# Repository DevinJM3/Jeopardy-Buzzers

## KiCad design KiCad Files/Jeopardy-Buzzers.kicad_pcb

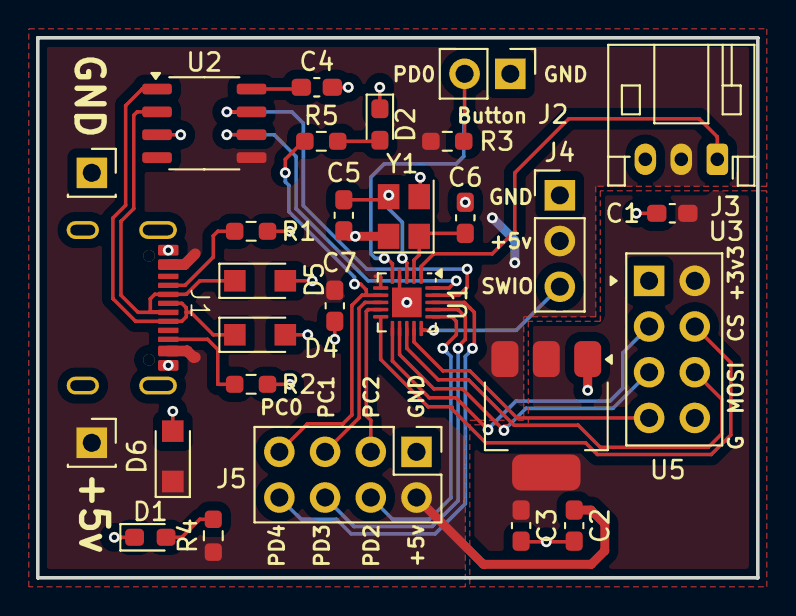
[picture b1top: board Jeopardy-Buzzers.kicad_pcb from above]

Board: 2 copper layers, 40.0 x 30.0 mm, 29 parts (0 on the bottom side), 28 nets.

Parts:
C1, C2: 10uF; C_0603_1608Metric_Pad1.08x0.95mm_HandSolder
C3: 22uF; C_0603_1608Metric_Pad1.08x0.95mm_HandSolder
C4, C7: 0.1uF; C_0603_1608Metric_Pad1.08x0.95mm_HandSolder
C5, C6: 12pF; C_0603_1608Metric_Pad1.08x0.95mm_HandSolder
D1, D2: LED; LED_0603_1608Metric_Pad1.05x0.95mm_HandSolder
D4, D5, D6: 5.1v; Nexperia_CFP3_SOD-123W
H1, H2: MountingHole_Pad; PinSocket_1x01_P2.54mm_Vertical
J1: USB_C_Receptacle_USB2.0_14P; Usb-C
J2: Conn_01x02_Pin; PinHeader_1x02_P2.54mm_Vertical
J3: Conn_01x03_Socket; JST_PH_S3B-PH-K_1x03_P2.00mm_Horizontal
J4: Conn_01x03_Socket; PinHeader_1x03_P2.54mm_Vertical
J5: Conn_02x04_Odd_Even; PinHeader_2x04_P2.54mm_Vertical
R1, R2: 5.1k; R_0603_1608Metric_Pad0.98x0.95mm_HandSolder
R3: 10k; R_0603_1608Metric_Pad0.98x0.95mm_HandSolder
R4, R5: 1k; R_0603_1608Metric_Pad0.98x0.95mm_HandSolder
U1: CH32V003FxUx; QFN-20-1EP_3x3mm_P0.4mm_EP1.65x1.65mm
U2: CH340N; SOP-8_3.9x4.9mm_P1.27mm
U3: NRF24L01_Breakout; nRF24L01_Breakout
U5: AMS1117-3.3; SOT-223-3_TabPin2
Y1: Crystal_24MHz; Crystal_SMD_3225-4Pin_3.2x2.5mm

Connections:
+3V3: C1.1, C3.1, U3.2 (VCC), U5.2 (VO)
+5V: C2.1, C7.2, D6.1 (K), H2.1, J1.A4 (VBUS), J3.2, J4.2, J5.2, R3.1, R4.1, U1.6 (VDD), U2.5 (VCC), U5.3 (VI)
GND: C1.2, C2.2, C3.2, C4.2, C5.2, C6.2, C7.1, D1.1 (K), D2.1 (K), D4.2 (A), D5.2 (A), D6.2 (A), H1.1, J1.A1 (GND), J2.1, J3.3, J4.1, J5.1, R1.2, R2.2, U1.4 (VSS), U1.21 (VSS), U2.3 (GND), U3.1 (GND), U3.8 (IRQ), U5.1 (GND), Y1.2, Y1.4
MCU_PC0: J5.7, R5.1, U1.7 (PC0)
MCU_PC1: J5.5, U1.8 (PC1)
MCU_PC2: J5.3, U1.9 (PC2)
MCU_PD2: J5.4, U1.16 (PD2)
MCU_PD3: J5.6, U1.17 (PD3)
MCU_PD4: J5.8, U1.18 (PD4)
MCU_SPI_CLK: U1.12 (PC5), U3.5 (SCK)
MCU_SPI_CS: U1.10 (PC3), U3.4 (~CSN)
MCU_SPI_MISO: U1.14 (PC7), U3.7 (MISO)
MCU_SPI_MOSI: U1.13 (PC6), U3.6 (MOSI)
MCU_SWIO: J4.3, U1.15 (PD1)
MCU_UART_RX: U1.20 (PD6), U2.6 (TXD)
MCU_UART_TX: U1.19 (PD5), U2.7 (RXD)
NRF24L01_CE: U1.11 (PC4), U3.3 (CE)
unnamed: D1.2 (A), R4.2
unnamed: D2.2 (A), R5.2
unnamed: J1.A5 (CC1), R1.1
unnamed: J1.B5 (CC2), R2.1
unnamed: J2.2, R3.2, U1.5 (PD0)
unnamed: C6.1, U1.2 (PA1), Y1.1
unnamed: C5.1, U1.3 (PA2), Y1.3
unnamed: C4.1, U2.8 (V3)
USB_D+: D4.1 (K), J1.A6 (D+), J1.B6 (D+), U2.1 (UD+)
USB_D-: D5.1 (K), J1.A7 (D-), J1.B7 (D-), U2.2 (UD-)
WS2812_LED: J3.1, U1.1 (PD7)

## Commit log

2025-04-28 Created the USB Power & Data Schematic, also added the MCU along with the NRF24L01
2025-04-28 Cleaned up the NRF24L01 & LDO
2025-04-28 Added AMS1117 LCSC Part#
2025-04-28 Added components to the schematic & added footprints to items
2025-04-29 Added crystal and passives for MCU, also added Zener diodes for USB Protection. Connected UART to the CH340N USB2UART chip
2025-04-30 Started Creating the USB-C connector footprint
2025-05-01 Added step files, and finished usb footprint
2025-05-06 Create LICENSE
2025-05-20 Changed footprints around, also added connectors
2025-05-21 moved parts around and started placing planes
2025-05-21 routed most of the traces, just need to pass ERC/DRC
2025-05-22 routed the USB and added my logo, text, and version number
2025-05-22 updated ERC Exclusions
2025-05-23 Added power led and user controlled led
2025-05-27 Moved Vias off of pads
2025-05-30 Updated LCSC Part Numbers
2025-06-11 Default config ch32 firmware
2025-07-03 Had the pinout for the addressable RGB cable backwards
2025-07-03 updated gitignore
